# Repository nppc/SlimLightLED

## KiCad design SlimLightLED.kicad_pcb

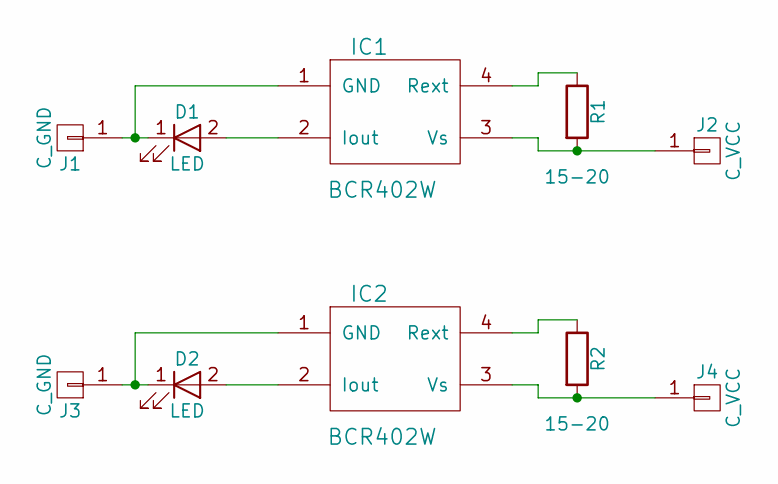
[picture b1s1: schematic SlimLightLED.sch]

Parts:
D1, D2: LED; 5730
IC1, IC2: BCR402W; BCR402
J1, J3: C_GND; Light_PAD
J2, J4: C_VCC; Light_PAD
R1, R2: 15-20; R_0402_NoSilk

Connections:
unnamed: D1.1 (K), IC1.1 (GND), J1.1
unnamed: D1.2 (A), IC1.2 (Iout)
unnamed: D2.1 (K), IC2.1 (GND), J3.1
unnamed: D2.2 (A), IC2.2 (Iout)
unnamed: IC1.3 (Vs), J2.1, R1.2
unnamed: IC1.4 (Rext), R1.1
unnamed: IC2.3 (Vs), J4.1, R2.2
unnamed: IC2.4 (Rext), R2.1

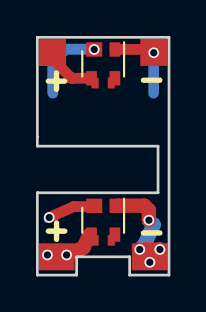
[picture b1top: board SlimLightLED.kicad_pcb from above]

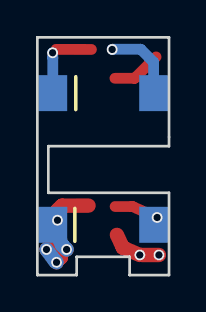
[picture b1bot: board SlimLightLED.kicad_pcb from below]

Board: 2 copper layers, 7.3 x 13.2 mm, 10 parts (2 on the bottom side), 8 nets.

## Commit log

2017-09-06 add another files
